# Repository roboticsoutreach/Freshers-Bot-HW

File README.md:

# Freshers-Bot-HW
hardware files used for the freshers bot

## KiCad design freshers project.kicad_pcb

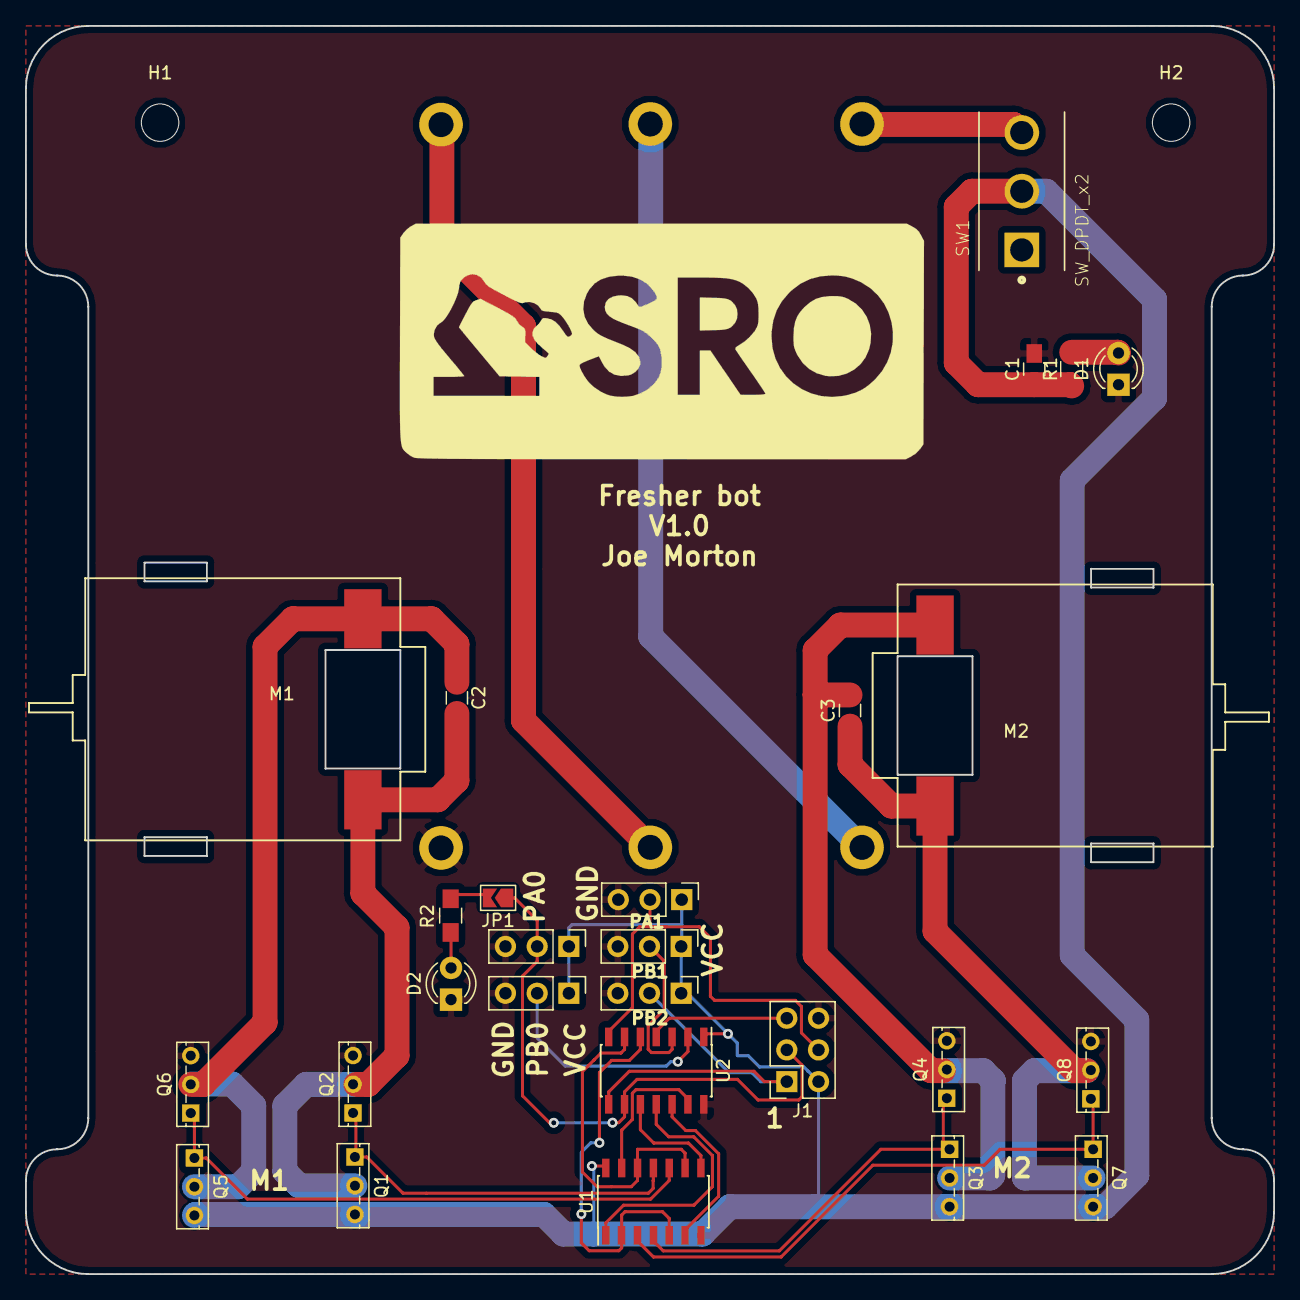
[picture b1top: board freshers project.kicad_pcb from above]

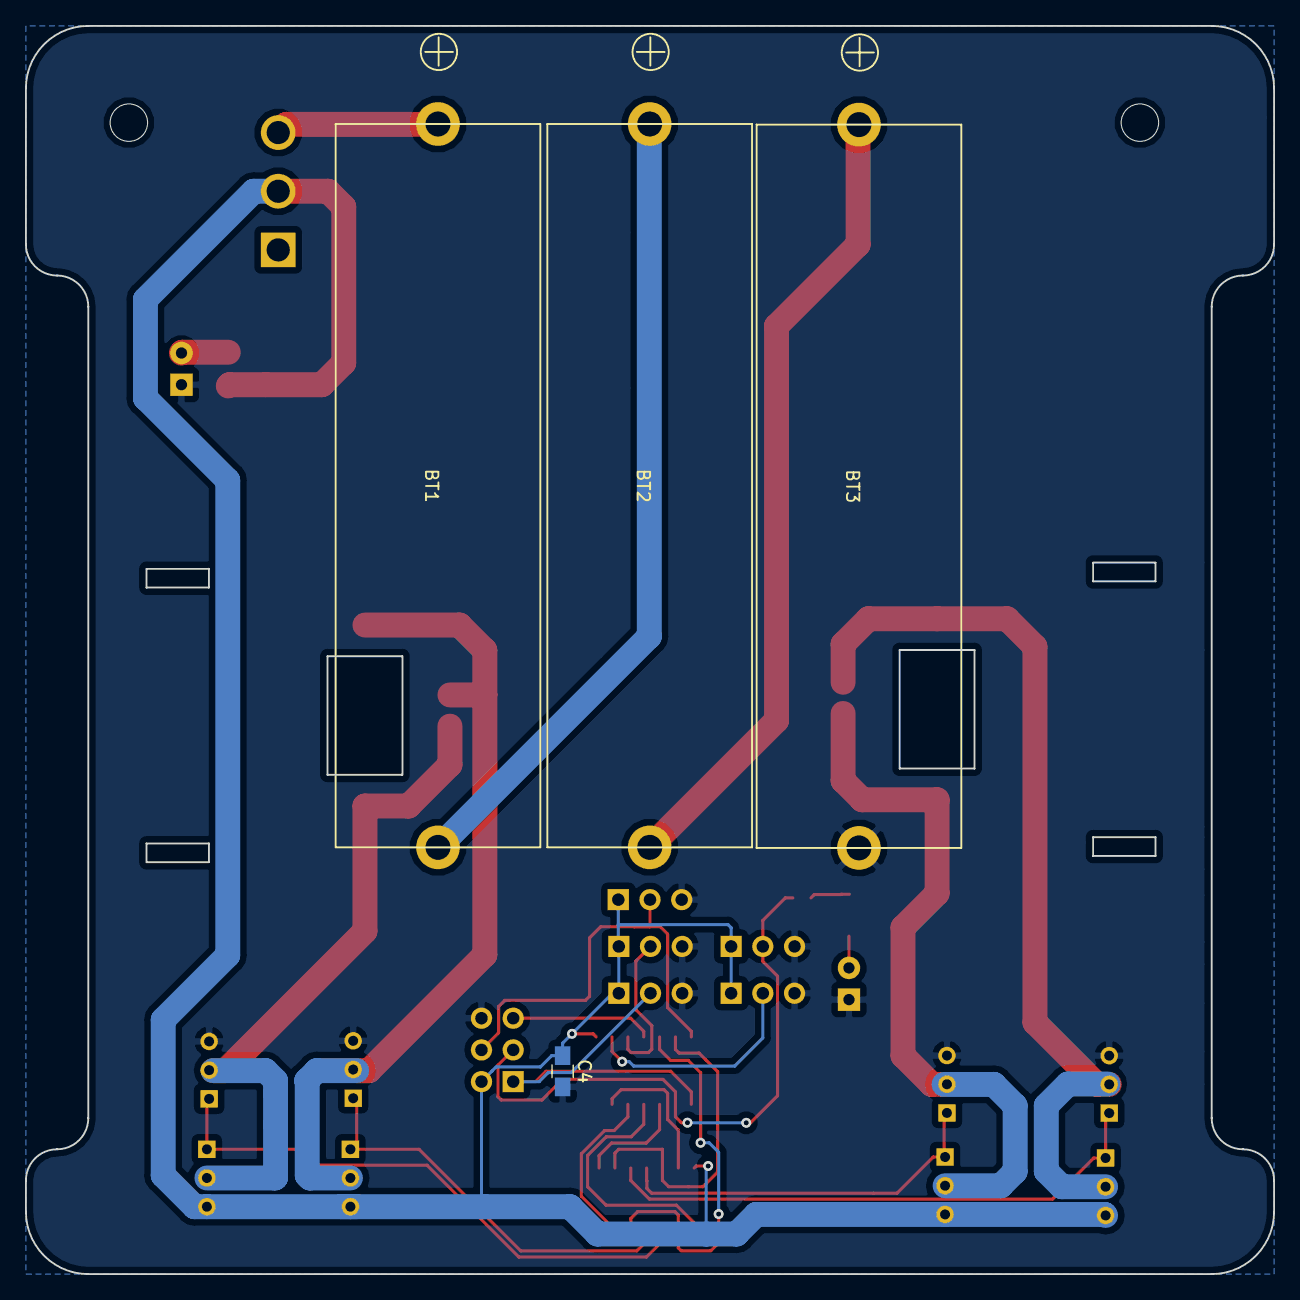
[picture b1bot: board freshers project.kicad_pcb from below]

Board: 2 copper layers, 100.0 x 100.0 mm, 33 parts (4 on the bottom side), 28 nets.

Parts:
BT1, BT2, BT3: Battery_Cell; AA battery holder
C1, C2, C3, C4: C; C_0805_HandSoldering
D1, D2: LED; LED_D3.0mm
H1, H2: MountingHole; MountingHole_3mm
J1: Conn_02x03_Odd_Even; Socket_Strip_Straight_2x03_Pitch2.54mm
J2, J3, J4, J5, J6: Conn_01x03; Socket_Strip_Straight_1x03_Pitch2.54mm
JP1: Jumper; SolderJumper-2_P1.3mm_Open_TrianglePad1.0x1.5mm
M1, M2: Motor_DC; SMDmotorMount
Q1, Q3, Q5, Q7: Q_PMOS_GDS; TO-251_IPAK_Vertical
Q2, Q4, Q6, Q8: Q_NMOS_GDS; TO-251_IPAK_Vertical
R1, R2: R; R_0805_HandSoldering
SW1: SW_DPDT_x2; TE_A101SYCQ04
U1: 4081; SOIC-14_3.9x8.7mm_Pitch1.27mm
U2: ATtiny24-20SSU; SOIC-14_3.9x8.7mm_Pitch1.27mm

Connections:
GND: BT3.2, C1.2, C4.2, D1.1, D2.1, J1.6, J2.3, J3.3, J4.3, J5.3, J6.3, Q2.3, Q4.3, Q6.3, Q8.3, U1.7, U2.14
M1A: U1.13, U2.13
M1B: U1.8, U2.10
M1PWM: U1.9, U1.12, U2.6
M2A: U1.6, U2.12
M2B: U1.1, U2.11
M2PWM: U1.2, U1.5, U2.5
MISO: J1.1, J6.2, U2.8
MOSI: J1.4, J4.2, U2.7
unnamed: BT1.1, SW1.3
unnamed: BT1.2, BT2.1
unnamed: BT2.2, BT3.1
unnamed: C2.1, M1.1, Q5.2, Q6.2
unnamed: C2.2, M1.2, Q1.2, Q2.2
unnamed: C3.1, M2.1, Q7.2, Q8.2
unnamed: C3.2, M2.2, Q3.2, Q4.2
unnamed: D1.2, R1.2
unnamed: D2.2, R2.2
unnamed: JP1.2, R2.1
unnamed: Q1.1, Q2.1, U1.11
unnamed: Q3.1, Q4.1, U1.4
unnamed: Q5.1, Q6.1, U1.10
unnamed: Q7.1, Q8.1, U1.3
PA4: J1.3, J3.2, JP1.1, U2.9
PB0: J2.2, U2.2
PB1: J5.2, U2.3
RESET: J1.5, U2.4
VCC: C1.1, C4.1, J1.2, J2.1, J3.1, J4.1, J5.1, J6.1, Q1.3, Q3.3, Q5.3, Q7.3, R1.1, SW1.2, U1.14, U2.1

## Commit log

2019-09-17 Added hardware files required to make a freshers bot
2019-09-17 Added specification
